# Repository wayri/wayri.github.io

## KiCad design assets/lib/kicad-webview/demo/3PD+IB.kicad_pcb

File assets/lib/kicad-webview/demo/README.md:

# Three-phase inverter demonstration

Author: Yawar Badri (wayri). Source: https://github.com/wayri/3-Phase-inverter-board

Pinned revision: `283f41b65c193abcc7e63c8c919dacdbccc89829`. This is a real owner-provided public design included for the viewer demonstration at the author's request. The upstream repository has no published license file; this snapshot is not represented as open-source/open-hardware licensed, and the library license does not establish a broader grant for the hardware design. Contact the owner for other uses.

The saved KiCad 6 PCB and all seven schematic sheets are retained unchanged. SHA-256 values and source URLs are recorded in PROVENANCE.json. The renderer displays available saved geometry, including saved zone fills; unsupported or unfilled constructs remain diagnosed. External KiCad-library model files are not included, so 3D component stand-ins are approximate.

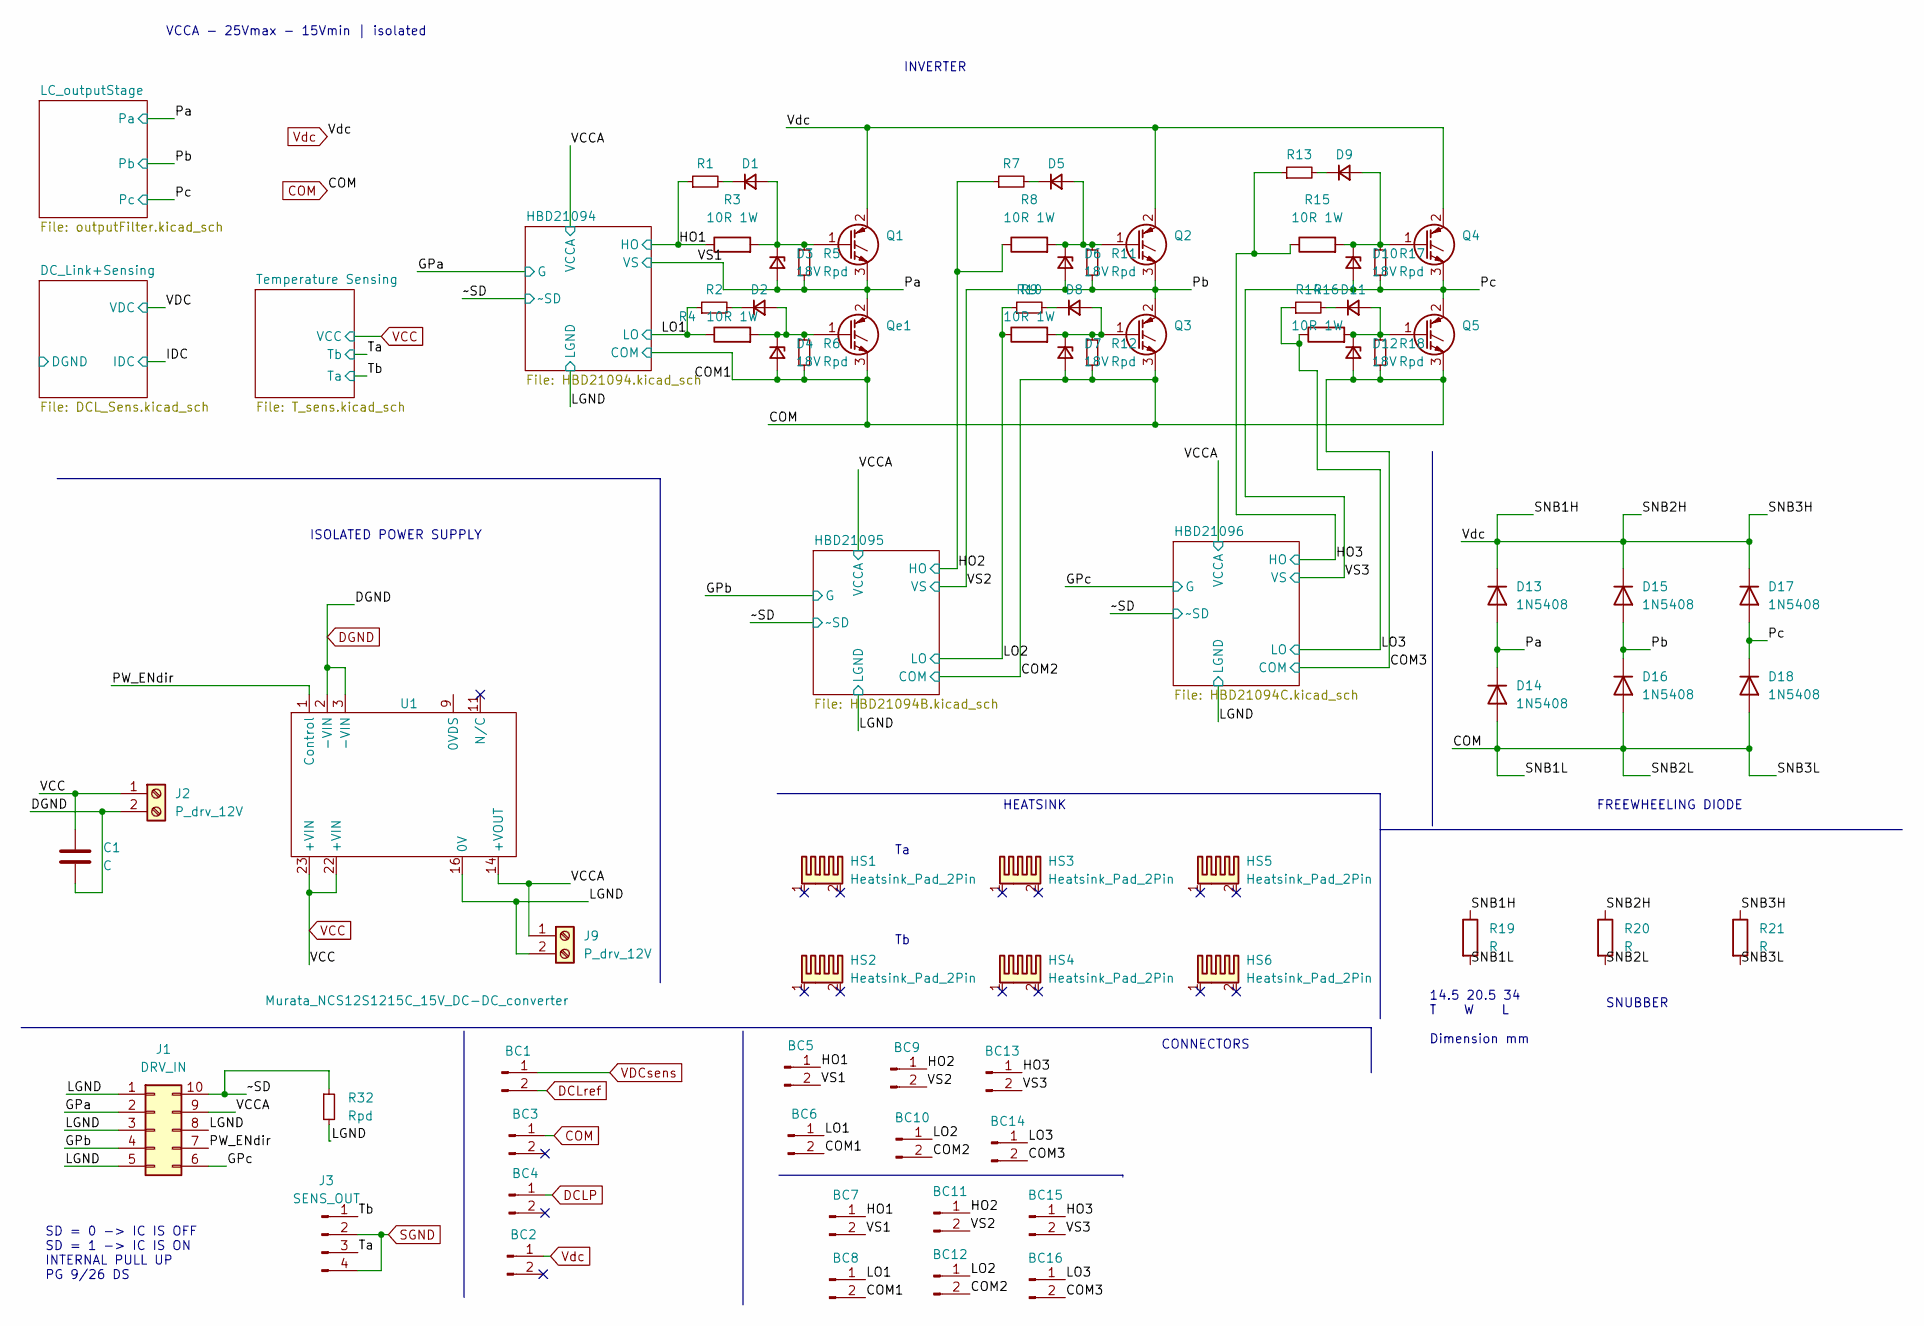
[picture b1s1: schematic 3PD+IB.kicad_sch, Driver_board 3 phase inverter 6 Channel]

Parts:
BC1, BC2, BC3, BC4, BC5, BC6, BC7, BC8, BC9, BC10, BC11, BC12, BC13, BC14, BC15, BC16: BoardConn; PhoenixContact_MCV_1,5_2-G-5.08_1x02_P5.08mm_Vertical
C1: C; CP_Radial_D7.5mm_P2.50mm
D1, D2, D5, D8, D9, D11: Dm; D_5W_P10.16mm_Horizontal
D3, D4, D6, D7, D10, D12: 18V; D_DO-41_SOD81_P10.16mm_Horizontal; Digikey id MMSZ18ET1G
D13, D14, D15, D16, D17, D18: 1N5408; D_DO-201AD_P15.24mm_Horizontal
HS1, HS2, HS3, HS4, HS5, HS6: Heatsink_Pad_2Pin; Heatsink_Fischer_SK104-STCB_35x13mm__2xDrill3.5mm_ScrewM3
J1: DRV_IN; PinHeader_2x05_P2.54mm_Vertical
J2, J9: P_drv_12V; TerminalBlock_Phoenix_MKDS-1,5-2_1x02_P5.00mm_Horizontal
J3: SENS_OUT; PinHeader_1x04_P2.54mm_Vertical
Q1, Q2, Q3, Q4, Q5: HGTG11N120CND; TO-247-3_Vertical
Qe1: HGTG11N120CND; TO-247-3_Vertical
R1, R2, R7, R9, R13, R14: 4R; R_Axial_DIN0309_L9.0mm_D3.2mm_P12.70mm_Horizontal
R3, R4, R8, R10, R15, R16: 10R 1W; R_Axial_DIN0309_L9.0mm_D3.2mm_P12.70mm_Horizontal
R5, R6, R11, R12, R17, R18: Rpd; R_Axial_DIN0207_L6.3mm_D2.5mm_P10.16mm_Horizontal
R19, R20, R21: R; R_Axial_DIN0918_L18.0mm_D9.0mm_P30.48mm_Horizontal
R32: Rpd; R_1210_3225Metric
U1: Murata_NCS12S1215C_15V_DC-DC_converter; murata_ncs12s1215c_15v

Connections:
/HO1: BC5.1, BC7.1, R1.1, R3.1; also elsewhere on the board
/HO2: BC9.1, BC11.1, R7.1, R8.1; also elsewhere on the board
/HO3: BC13.1, BC15.1, R13.1, R15.1; also elsewhere on the board
/LGND: J1.1, J1.3, J1.5, J1.8, J9.2, R32.2, U1.16 (0V); also elsewhere on the board
/LO2: BC10.1, BC12.1, R9.1, R10.1; also elsewhere on the board
/LO3: BC14.1, BC16.1, R14.1, R16.1; also elsewhere on the board
/PW_ENdir: J1.7, U1.1 (Control)
/Pa: BC5.2, BC7.2, D3.2 (A), D13.2 (A), D14.1 (K), Q1.3 (E), Qe1.2 (C), R5.2; also elsewhere on the board
/Pb: BC9.2, BC11.2, D6.2 (A), D15.2 (A), D16.1 (K), Q2.3 (E), Q3.2 (C), R11.2; also elsewhere on the board
/Pc: BC13.2, BC15.2, D10.2 (A), D17.2 (A), D18.1 (K), Q4.3 (E), Q5.2 (C), R17.2; also elsewhere on the board
/Ta: J3.3; also elsewhere on the board
/Tb: J3.1; also elsewhere on the board
/VCCA: J1.9, J9.1, U1.14 (+VOUT); also elsewhere on the board
/~SD: J1.10, R32.1; also elsewhere on the board
DCLP: BC4.1; also elsewhere on the board
DCLref: BC1.2; also elsewhere on the board
DGND: C1.2, J2.2, U1.2 (-VIN), U1.3 (-VIN)
GPa: J1.2; also elsewhere on the board
GPb: J1.4; also elsewhere on the board
GPc: J1.6; also elsewhere on the board
unnamed: D1.1 (K), R1.2
unnamed: D1.2 (A), D3.1 (K), Q1.1 (G), R3.2, R5.1
unnamed: D2.1 (K), R2.2
unnamed: D2.2 (A), D4.1 (K), Qe1.1 (G), R4.2, R6.1
unnamed: D5.1 (K), R7.2
unnamed: D5.2 (A), D6.1 (K), Q2.1 (G), R8.2, R11.1
unnamed: D7.1 (K), D8.2 (A), Q3.1 (G), R10.2, R12.1
unnamed: D8.1 (K), R9.2
unnamed: D9.1 (K), R13.2
unnamed: D9.2 (A), D10.1 (K), Q4.1 (G), R15.2, R17.1
unnamed: D11.1 (K), R14.2
unnamed: D11.2 (A), D12.1 (K), Q5.1 (G), R16.2, R18.1
SGND: J3.2, J3.4; also elsewhere on the board
VCC: C1.1, J2.1, U1.22 (+VIN), U1.23 (+VIN)
VDCsens: BC1.1; also elsewhere on the board
Vdc: BC2.1, D13.1 (K), D15.1 (K), D17.1 (K), Q1.2 (C), Q2.2 (C), Q4.2 (C), R19.1, R20.1, R21.1; also elsewhere on the board

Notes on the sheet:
CONNECTORS
INVERTER
FREEWHEELING DIODE
14.5 20.5 34 T W L Dimension mm
ISOLATED POWER SUPPLY
SD = 0 -> IC IS OFF SD = 1 -> IC IS ON INTERNAL PULL UP PG 9/26 DS
HEATSINK
SNUBBER
VCCA - 25Vmax - 15Vmin | isolated

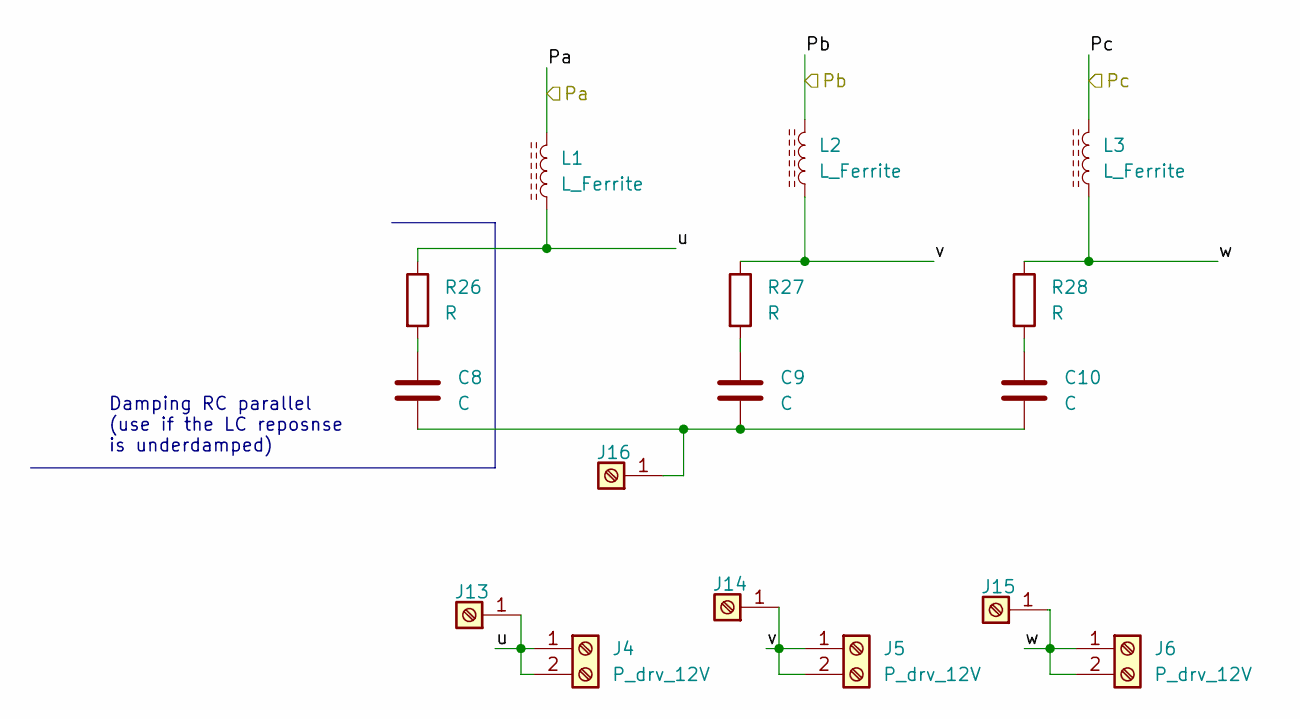
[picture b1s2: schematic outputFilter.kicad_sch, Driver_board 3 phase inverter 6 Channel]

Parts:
C8, C9, C10: C; C_Rect_L26.5mm_W10.5mm_P22.50mm_MKS4
J4, J5, J6: P_drv_12V; TerminalBlock_Phoenix_MKDS-1,5-2_1x02_P5.00mm_Horizontal
J13, J14, J15, J16: Screw_Terminal_01x01; Banana_Jack_1Pin
L1, L2, L3: L_Ferrite; L_Toroid_Vertical_L41.9mm_W19.1mm_P15.80mm_Vishay_TJ7
R26, R27, R28: R; R_Axial_Power_L38.0mm_W9.0mm_P40.64mm

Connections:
/LC_outputStage/u: J4.1, J4.2, J13.1, L1.1, R26.1
/LC_outputStage/v: J5.1, J5.2, J14.1, L2.1, R27.1
/LC_outputStage/w: J6.1, J6.2, J15.1, L3.1, R28.1
/Pa: L1.2; also elsewhere on the board
/Pb: L2.2; also elsewhere on the board
/Pc: L3.2; also elsewhere on the board
unnamed: C8.2, R26.2
unnamed: C9.2, R27.2
unnamed: C8.1, C9.1, C10.1, J16.1
unnamed: C10.2, R28.2

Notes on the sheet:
Damping RC parallel (use if the LC reposnse is underdamped)

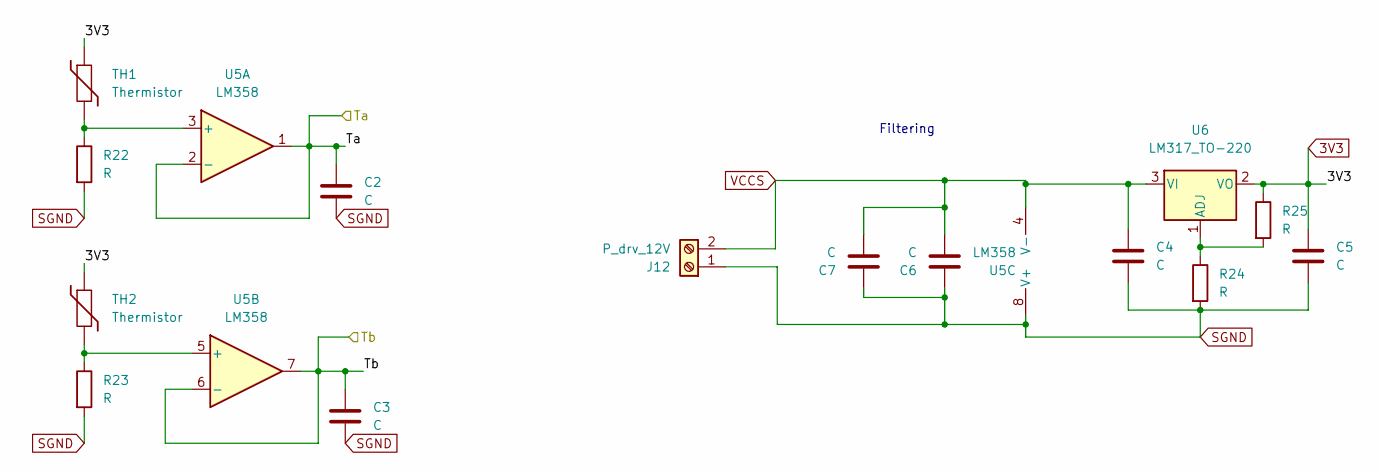
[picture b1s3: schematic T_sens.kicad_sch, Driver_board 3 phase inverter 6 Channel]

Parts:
C2, C3, C6, C7: C; C_Disc_D4.3mm_W1.9mm_P5.00mm
C4, C5: C; CP_Radial_D7.5mm_P2.50mm
J12: P_drv_12V; TerminalBlock_Phoenix_MKDS-1,5-2_1x02_P5.00mm_Horizontal
R22, R23, R24, R25: R; R_Axial_DIN0207_L6.3mm_D2.5mm_P7.62mm_Horizontal
TH1, TH2: Thermistor; R_Axial_DIN0204_L3.6mm_D1.6mm_P5.08mm_Horizontal
U5: LM358; DIP-8_W7.62mm_LongPads
U6: LM317_TO-220; TO-220-3_Vertical

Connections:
3V3: C5.1, R25.1, TH1.1, TH2.1, U6.2 (VO)
/Ta: C3.1, U5.6 (-), U5.7; also elsewhere on the board
/Tb: C2.1, U5.1, U5.2 (-); also elsewhere on the board
unnamed: R22.1, TH1.2, U5.3 (+)
unnamed: R23.1, TH2.2, U5.5 (+)
unnamed: R24.1, R25.2, U6.1 (ADJ)
SGND: C2.2, C3.2, C4.2, C5.2, C6.1, C7.1, J12.1, R22.2, R23.2, R24.2, U5.8 (V+); also elsewhere on the board
VCCS: C4.1, C6.2, C7.2, J12.2, U5.4 (V-), U6.3 (VI)

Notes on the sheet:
Filtering

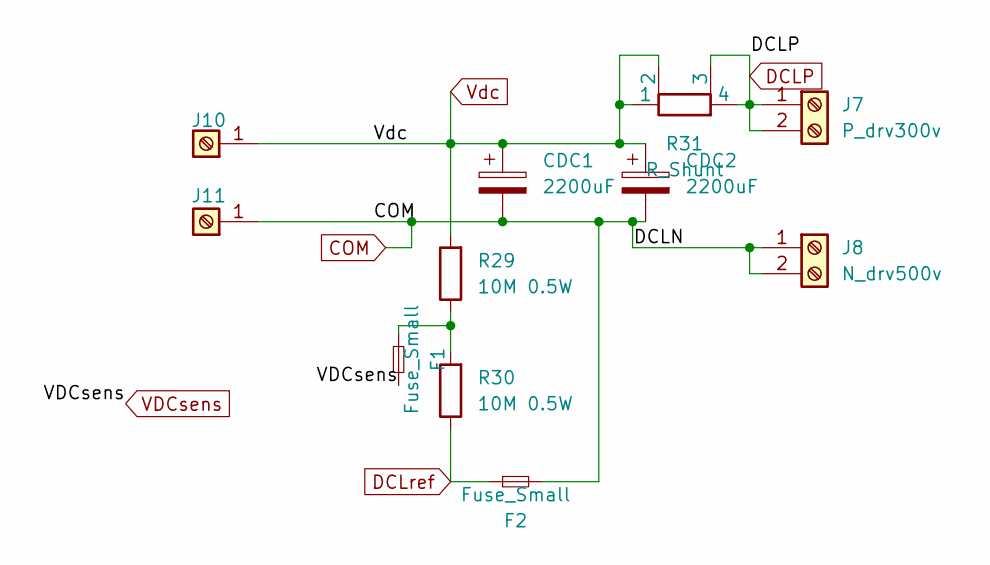
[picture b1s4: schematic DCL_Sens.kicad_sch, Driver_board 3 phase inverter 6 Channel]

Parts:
CDC1, CDC2: 2200uF; CP_Radial_D35.0mm_P10.00mm_SnapIn
F1, F2: Fuse_Small; Fuse_2512_6332Metric
J7: P_drv300v; TerminalBlock_Phoenix_MKDS-1,5-2_1x02_P5.00mm_Horizontal
J8: N_drv500v; TerminalBlock_Phoenix_MKDS-1,5-2_1x02_P5.00mm_Horizontal
J10, J11: Screw_Terminal_01x01; Banana_Jack_1Pin
R29, R30: 10M 0.5W; R_Axial_DIN0309_L9.0mm_D3.2mm_P12.70mm_Horizontal
R31: R_Shunt; R_Axial_Shunt_L35.3mm_W9.5mm_PS25.40mm_P38.10mm

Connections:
DCLP: J7.1, J7.2, R31.3, R31.4; also elsewhere on the board
DCLref: F2.1, R30.1; also elsewhere on the board
unnamed: F1.2, R29.1, R30.2
VDCsens: F1.1; also elsewhere on the board
Vdc: CDC1.1, CDC2.1, J10.1, R29.2, R31.1, R31.2; also elsewhere on the board

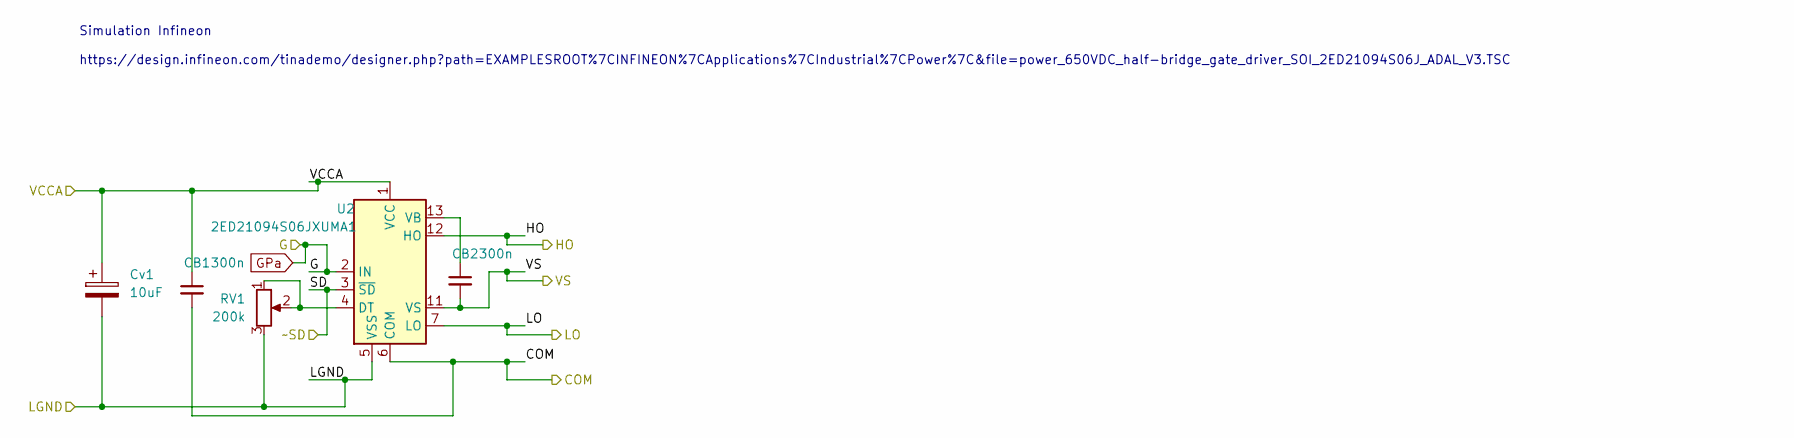
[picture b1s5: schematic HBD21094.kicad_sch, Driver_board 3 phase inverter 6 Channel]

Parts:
CB1, CB2: 300n; C_Axial_L3.8mm_D2.6mm_P7.50mm_Horizontal
Cv1: 10uF; CP_Radial_D8.0mm_P2.50mm
RV1: 200k; Potentiometer_Bourns_3296W_Vertical
U2: 2ED21094S06JXUMA1; SOIC-14_3.9x8.7mm_P1.27mm; LCSC part No. C537551

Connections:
/HO1: U2.12 (HO); also elsewhere on the board
/LGND: Cv1.2, RV1.3, U2.5 (VSS); also elsewhere on the board
/Pa: CB2.2, U2.11 (VS); also elsewhere on the board
/VCCA: CB1.1, Cv1.1, U2.1 (VCC); also elsewhere on the board
/~SD: U2.3 (~SD); also elsewhere on the board
GPa: U2.2 (IN); also elsewhere on the board
unnamed: CB2.1, U2.13 (VB)
unnamed: RV1.1, RV1.2, U2.4 (DT)

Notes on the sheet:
Simulation Infineon https://design.infineon.com/tinademo/designer.php?path=EXAMPLESROOT%7CINFINEON%7CApplications%7CIndustrial%7CPower%7C&file=power_650VDC_half-bridge_gate_driver_SOI_2ED21094S06J_ADAL_V3.TSC

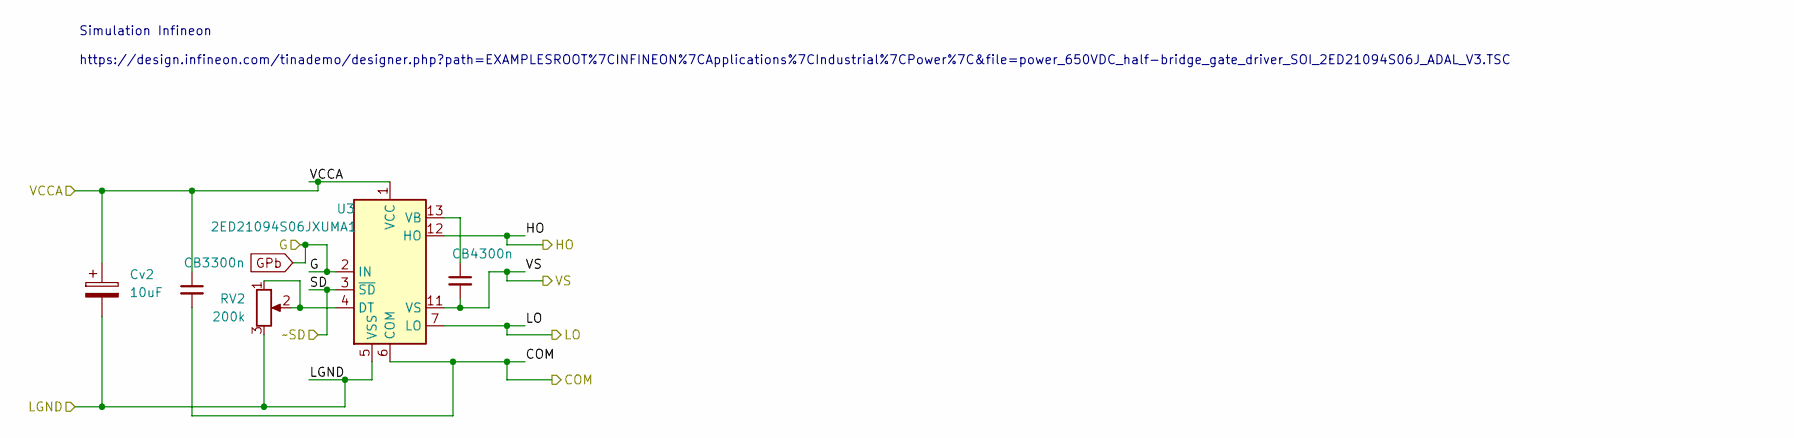
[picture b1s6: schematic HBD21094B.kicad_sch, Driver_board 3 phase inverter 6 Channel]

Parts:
CB3, CB4: 300n; C_Axial_L3.8mm_D2.6mm_P7.50mm_Horizontal
Cv2: 10uF; CP_Radial_D8.0mm_P2.50mm
RV2: 200k; Potentiometer_Bourns_3296W_Vertical
U3: 2ED21094S06JXUMA1; SOIC-14_3.9x8.7mm_P1.27mm; LCSC part No. C537551

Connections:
/HO2: U3.12 (HO); also elsewhere on the board
/LGND: Cv2.2, RV2.3, U3.5 (VSS); also elsewhere on the board
/LO2: U3.7 (LO); also elsewhere on the board
/Pb: CB4.2, U3.11 (VS); also elsewhere on the board
/VCCA: CB3.1, Cv2.1, U3.1 (VCC); also elsewhere on the board
/~SD: U3.3 (~SD); also elsewhere on the board
GPb: U3.2 (IN); also elsewhere on the board
unnamed: CB4.1, U3.13 (VB)
unnamed: RV2.1, RV2.2, U3.4 (DT)

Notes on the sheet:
Simulation Infineon https://design.infineon.com/tinademo/designer.php?path=EXAMPLESROOT%7CINFINEON%7CApplications%7CIndustrial%7CPower%7C&file=power_650VDC_half-bridge_gate_driver_SOI_2ED21094S06J_ADAL_V3.TSC

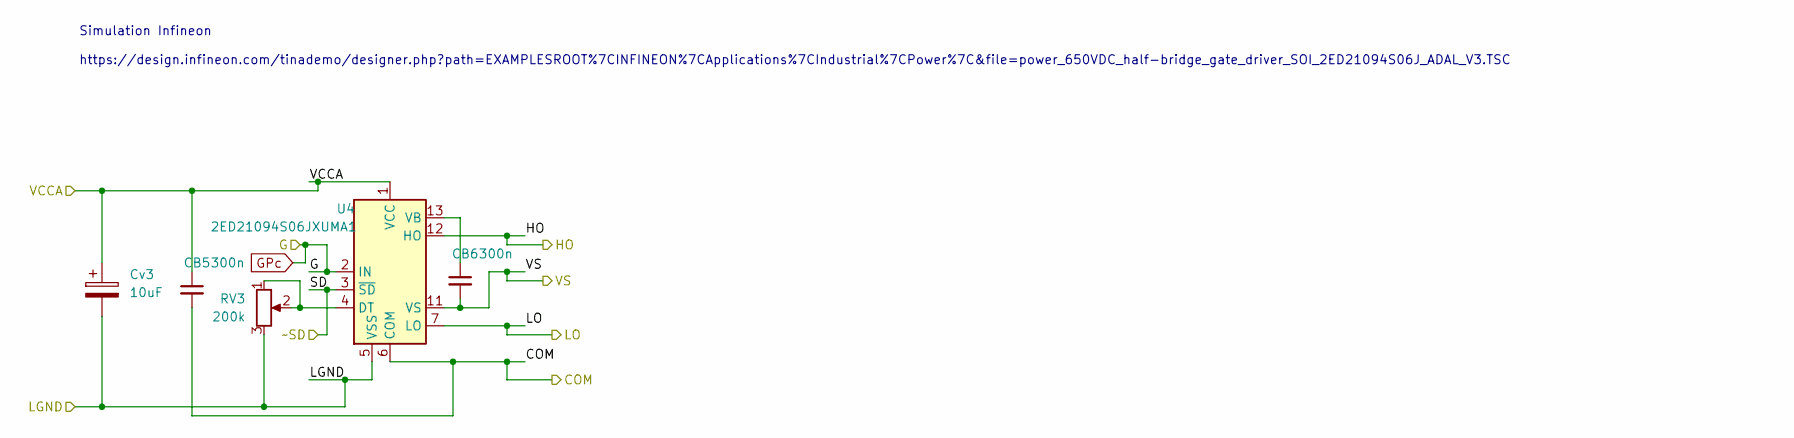
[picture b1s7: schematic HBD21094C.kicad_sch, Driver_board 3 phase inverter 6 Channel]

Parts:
CB5, CB6: 300n; C_Axial_L3.8mm_D2.6mm_P7.50mm_Horizontal
Cv3: 10uF; CP_Radial_D8.0mm_P2.50mm
RV3: 200k; Potentiometer_Bourns_3296W_Vertical
U4: 2ED21094S06JXUMA1; SOIC-14_3.9x8.7mm_P1.27mm; LCSC part No. C537551

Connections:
/HO3: U4.12 (HO); also elsewhere on the board
/LGND: Cv3.2, RV3.3, U4.5 (VSS); also elsewhere on the board
/LO3: U4.7 (LO); also elsewhere on the board
/Pc: CB6.2, U4.11 (VS); also elsewhere on the board
/VCCA: CB5.1, Cv3.1, U4.1 (VCC); also elsewhere on the board
/~SD: U4.3 (~SD); also elsewhere on the board
GPc: U4.2 (IN); also elsewhere on the board
unnamed: CB6.1, U4.13 (VB)
unnamed: RV3.1, RV3.2, U4.4 (DT)

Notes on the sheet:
Simulation Infineon https://design.infineon.com/tinademo/designer.php?path=EXAMPLESROOT%7CINFINEON%7CApplications%7CIndustrial%7CPower%7C&file=power_650VDC_half-bridge_gate_driver_SOI_2ED21094S06J_ADAL_V3.TSC

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
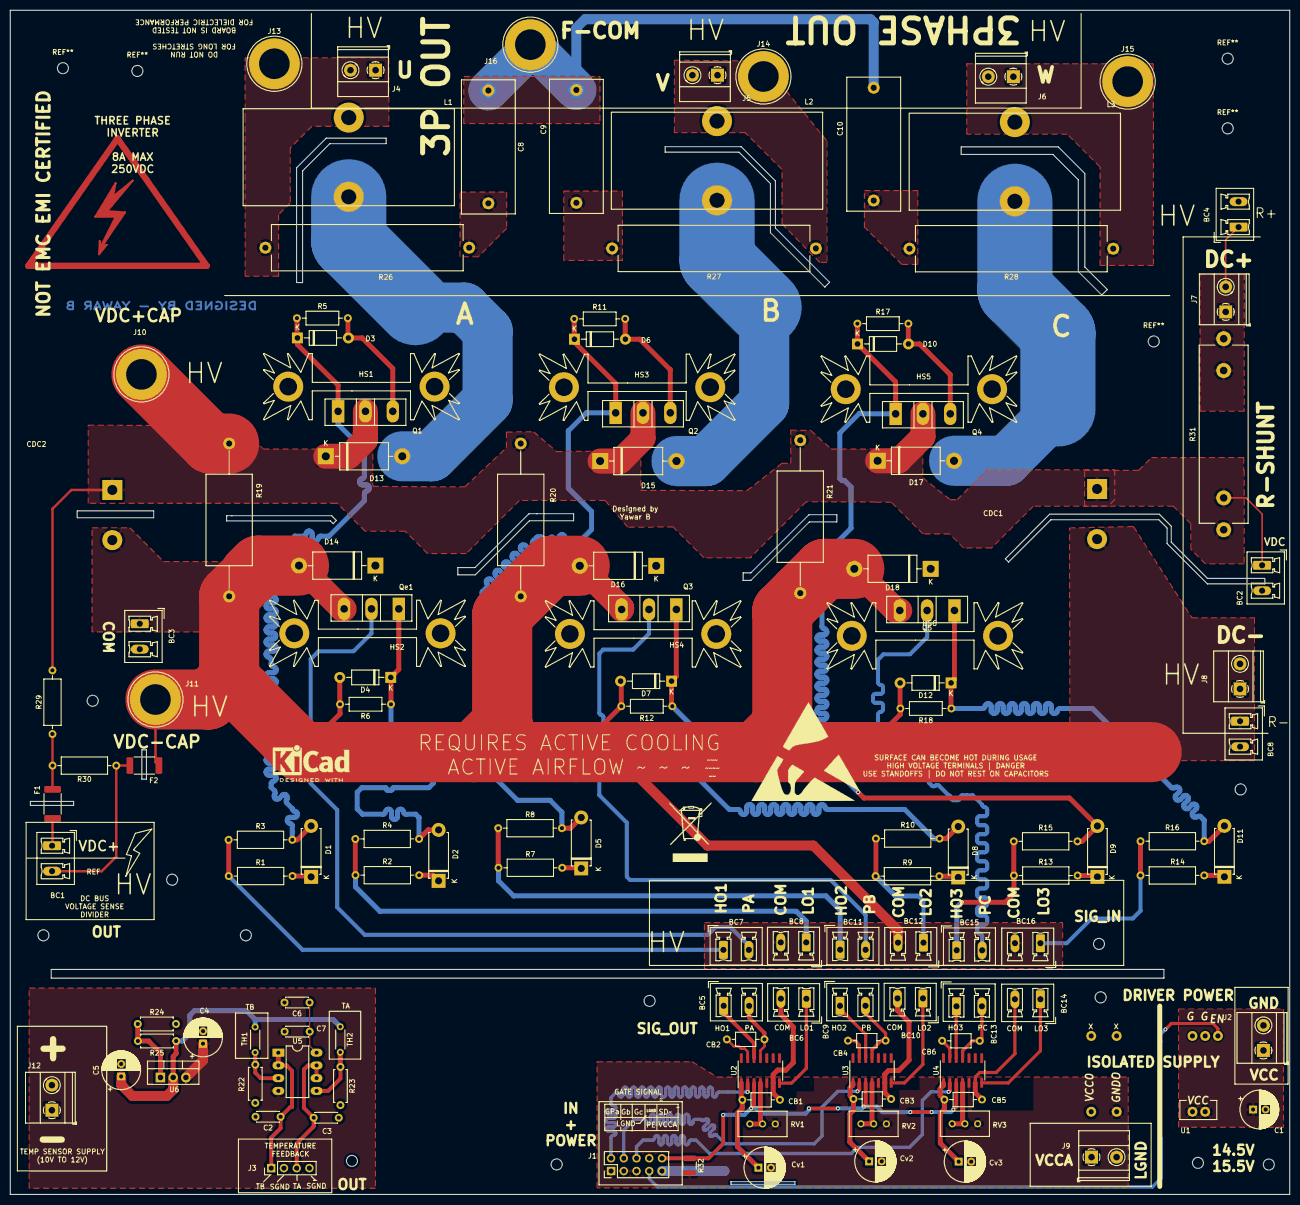
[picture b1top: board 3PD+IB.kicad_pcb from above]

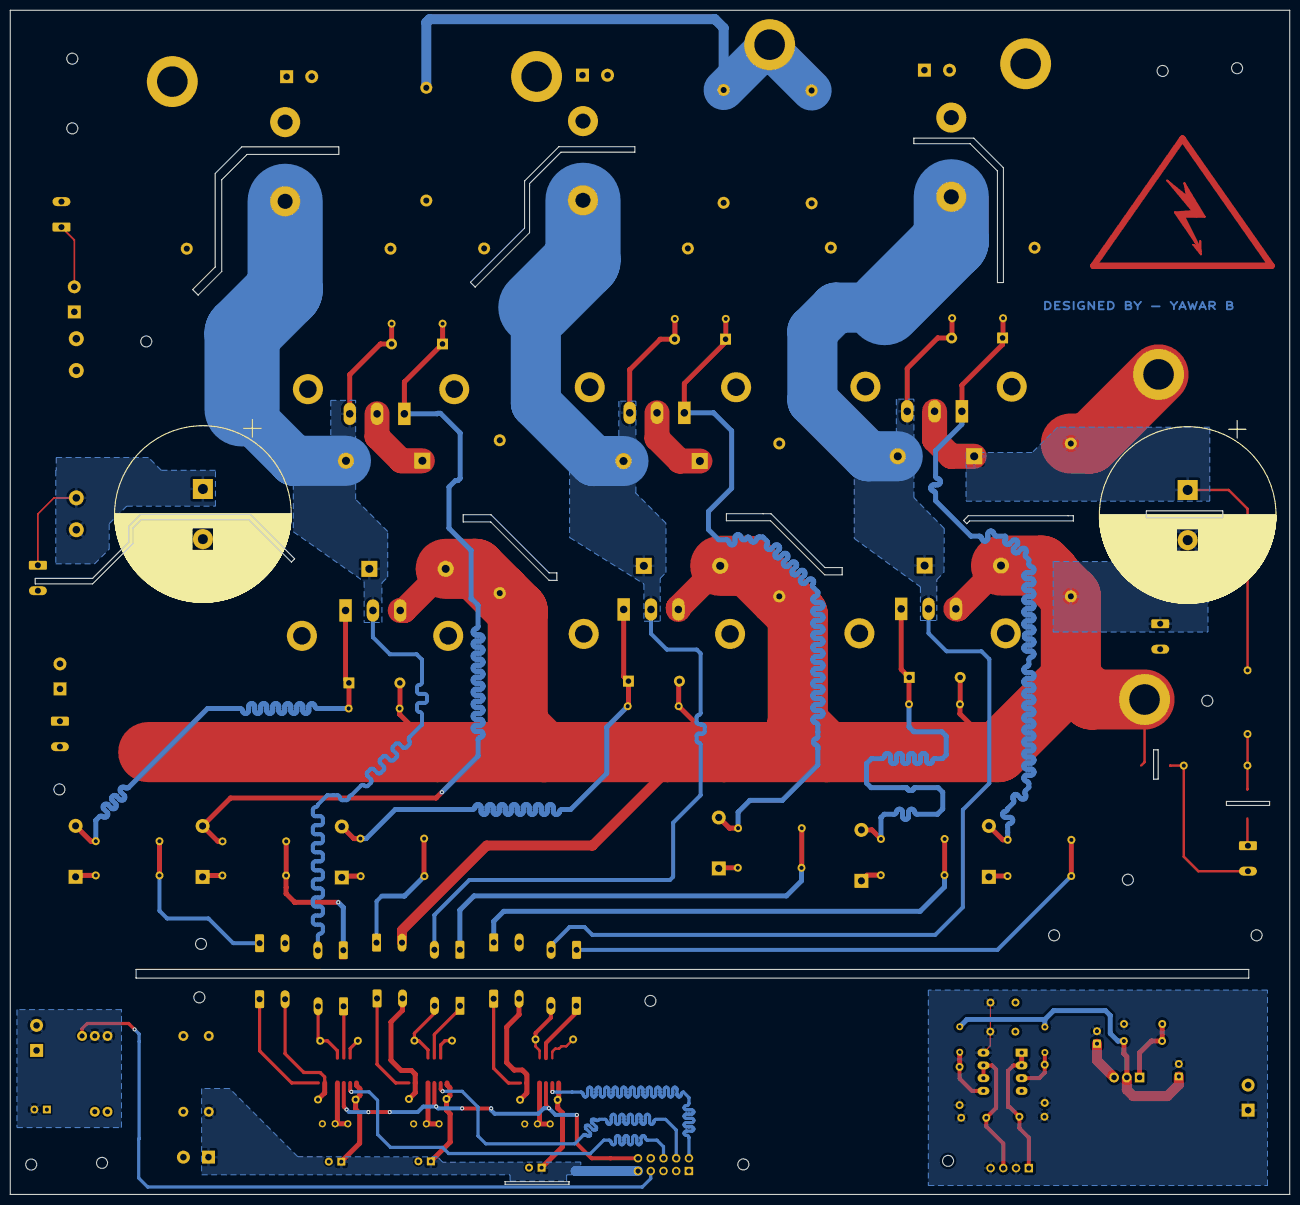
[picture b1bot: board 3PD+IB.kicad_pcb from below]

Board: 2 copper layers, 255.2 x 236.2 mm, 132 parts (2 on the bottom side), 57 nets.

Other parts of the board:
BC8#2: BoardConn; PhoenixContact_MCV_1,5_2-G-5.08_1x02_P5.08mm_Vertical

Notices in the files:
assets/demos/public-hardware/olimex-models.kicad_pcb:
(C) 2025
